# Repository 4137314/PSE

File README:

PSE - Power Supply Emulator
===========================

Version: 1.0
Author: 4137314
License: GNU General Public License v3.0

Purpose
-------
PSE is a KiCad project designed to emulate power supply circuits
for testing and prototyping purposes. It includes both schematic
and PCB layout files suitable for educational and development use.

Installation
------------
To obtain the project, clone the repository using Git:

    git clone https://github.com/4137314/PSE.git
    cd PSE

Open the file "PSE.kicad_pro" in KiCad to access the full project.

Usage
-----
- Inspect the schematic via "PSE.kicad_sch".
- Review the PCB layout in "PSE.kicad_pcb".
- Generate manufacturing files (Gerber, BOM, Drill) if needed.

Ensure all libraries and footprints referenced by the project are
available in your KiCad environment.

License
-------
This project is licensed under the GNU General Public License v3.0.
Refer to the LICENSE file in this repository for the full license text.

Reporting Bugs / Contributing
-----------------------------
Report bugs or suggest improvements via GitHub Issues. Contributions
are welcome under the same GPLv3 license.

Contact
-------
4137314
https://github.com/4137314/PSE

=======================================================================

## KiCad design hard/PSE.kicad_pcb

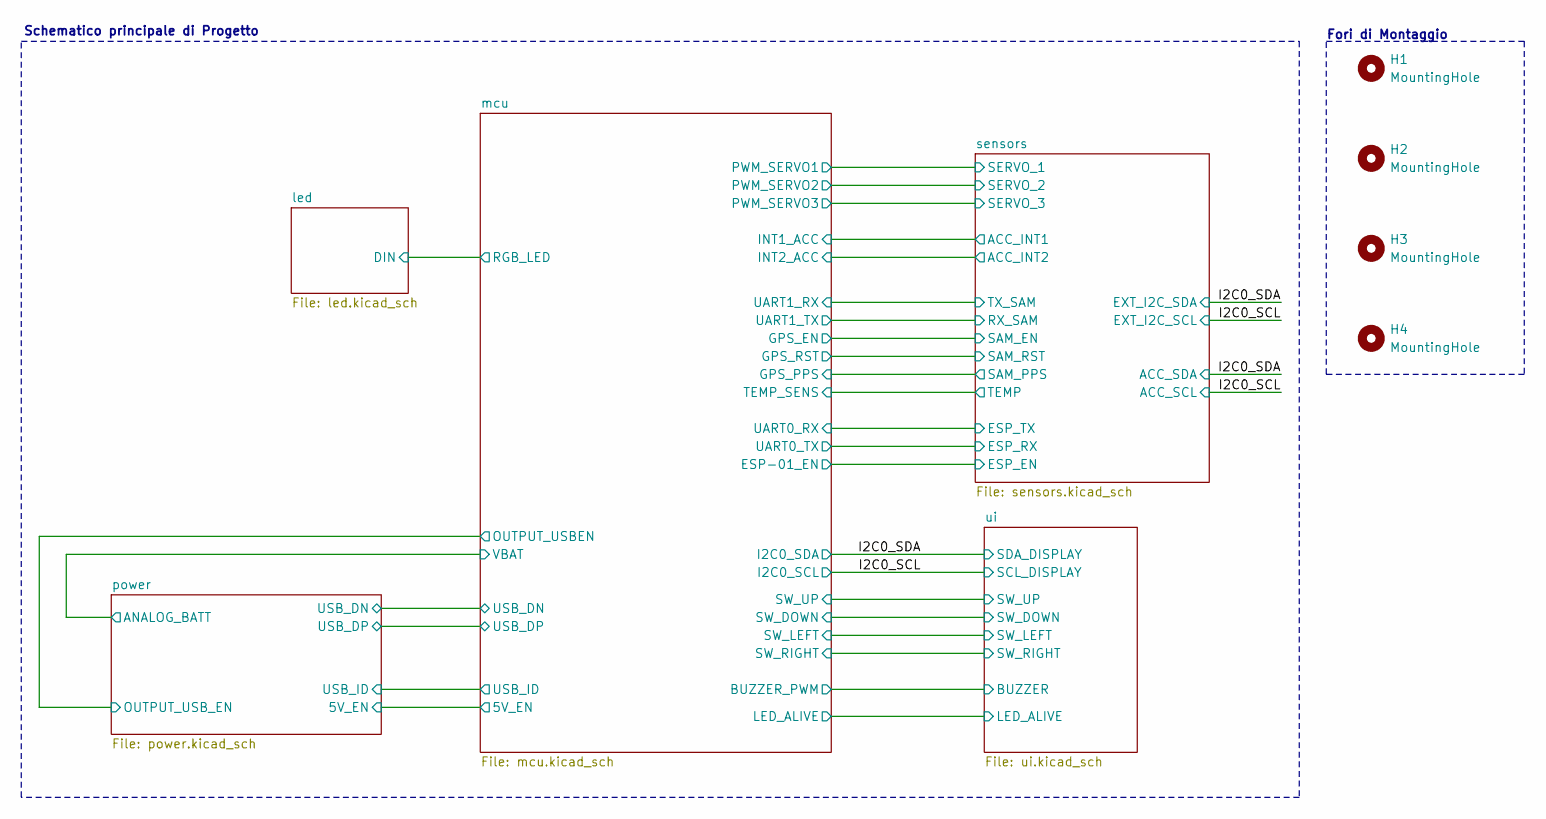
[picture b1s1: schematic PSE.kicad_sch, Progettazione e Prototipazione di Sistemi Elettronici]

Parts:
H1, H2, H3, H4: MountingHole; MountingHole_3.2mm_M3_Pad_Via

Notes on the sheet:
Fori di Montaggio
Schematico principale di Progetto

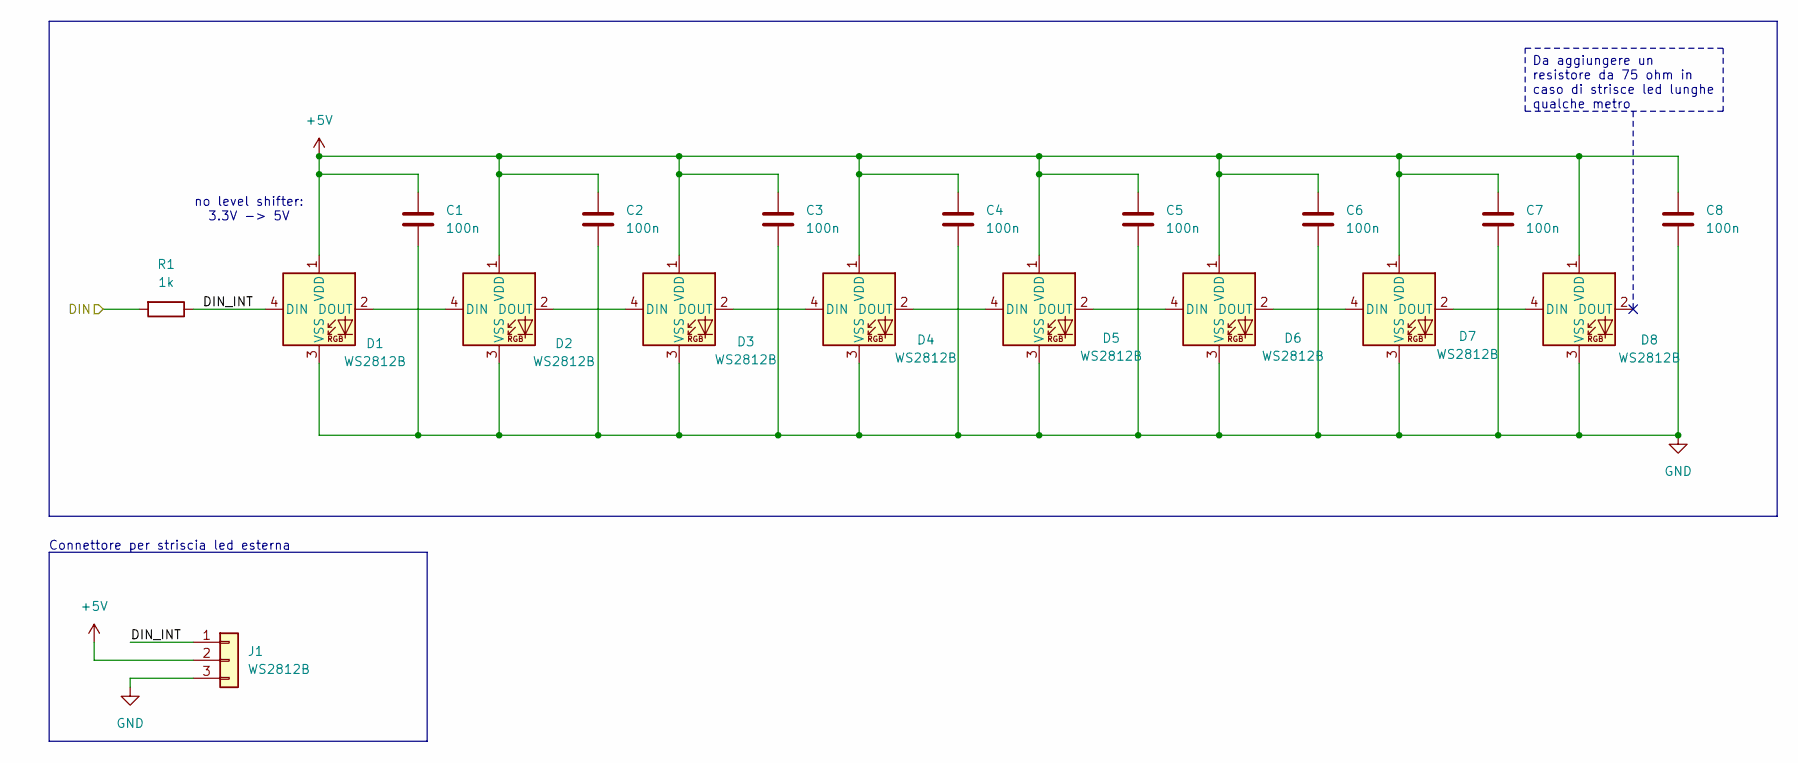
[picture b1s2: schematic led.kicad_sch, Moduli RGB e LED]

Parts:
C1, C2, C3, C4, C5, C6, C7, C8: 100n; C_0603_1608Metric
D1, D2, D3, D4, D5, D6, D7, D8: WS2812B; LED_WS2812B_PLCC4_5.0x5.0mm_P3.2mm
J1: WS2812B; PinHeader_1x03_P2.54mm_Vertical
R1: 1k; R_0603_1608Metric

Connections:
+5V: C1.1, C2.1, C3.1, C4.1, C5.1, C6.1, C7.1, C8.1, D1.1 (VDD), D2.1 (VDD), D3.1 (VDD), D4.1 (VDD), D5.1 (VDD), D6.1 (VDD), D7.1 (VDD), D8.1 (VDD), J1.2; also elsewhere on the board
/led/DIN: R1.2; also elsewhere on the board
/led/DIN_INT: D1.4 (DIN), J1.1, R1.1
GND: C1.2, C2.2, C3.2, C4.2, C5.2, C6.2, C7.2, C8.2, D1.3 (VSS), D2.3 (VSS), D3.3 (VSS), D4.3 (VSS), D5.3 (VSS), D6.3 (VSS), D7.3 (VSS), D8.3 (VSS), J1.3; also elsewhere on the board
unnamed: D1.2 (DOUT), D2.4 (DIN)
unnamed: D2.2 (DOUT), D3.4 (DIN)
unnamed: D3.2 (DOUT), D4.4 (DIN)
unnamed: D4.2 (DOUT), D5.4 (DIN)
unnamed: D5.2 (DOUT), D6.4 (DIN)
unnamed: D6.2 (DOUT), D7.4 (DIN)
unnamed: D7.2 (DOUT), D8.4 (DIN)

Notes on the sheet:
no level shifter: 3.3V -> 5V
Connettore per striscia led esterna
Da aggiungere un resistore da 75 ohm in caso di strisce led lunghe qualche metro

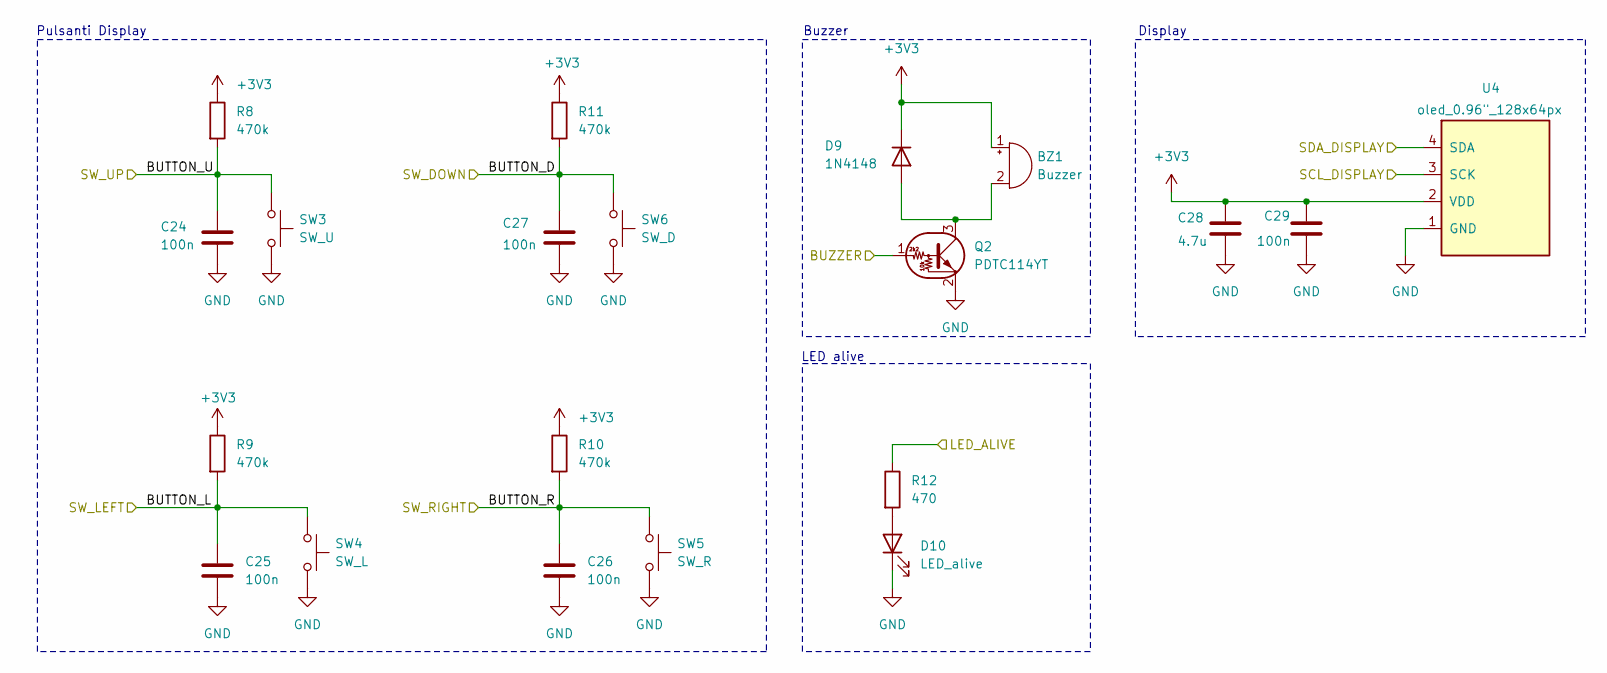
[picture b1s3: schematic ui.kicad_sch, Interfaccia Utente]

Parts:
BZ1: Buzzer; Buzzer_12x9.5RM7.6
C24, C25, C26, C27, C29: 100n; C_0603_1608Metric
C28: 4.7u; C_0603_1608Metric
D9: 1N4148; D_SOD-123
D10: LED_alive; LED_0603_1608Metric
Q2: PDTC114YT; SOT-23
R8, R9, R10, R11: 470k; R_0603_1608Metric
R12: 470; R_0603_1608Metric
SW3: SW_U; SW_SPST_EVQP0
SW4: SW_L; SW_SPST_EVQP0
SW5: SW_R; SW_SPST_EVQP0
SW6: SW_D; SW_SPST_EVQP0
U4: oled_0.96"_128x64px; PinHeader_1x04_P2.54mm_Vertical

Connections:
+3V3: BZ1.1 (+), C28.1, C29.1, D9.1 (K), R8.1, R9.1, R10.1, R11.1, U4.2 (VDD); also elsewhere on the board
/I2C0_SCL: U4.3 (SCK); also elsewhere on the board
/I2C0_SDA: U4.4 (SDA); also elsewhere on the board
/mcu/BUZZER_PWM: Q2.1 (B); also elsewhere on the board
/mcu/LED_ALIVE: R12.1; also elsewhere on the board
/ui/BUTTON_D: C27.1, R11.2, SW6.1; also elsewhere on the board
/ui/BUTTON_L: C25.1, R9.2, SW4.1; also elsewhere on the board
/ui/BUTTON_R: C26.1, R10.2, SW5.1; also elsewhere on the board
/ui/BUTTON_U: C24.1, R8.2, SW3.1; also elsewhere on the board
GND: C24.2, C25.2, C26.2, C27.2, C28.2, C29.2, D10.1 (K), Q2.2 (E), SW3.2, SW4.2, SW5.2, SW6.2, U4.1 (GND); also elsewhere on the board
unnamed: BZ1.2 (-), D9.2 (A), Q2.3 (C)
unnamed: D10.2 (A), R12.2

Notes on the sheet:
Pulsanti Display
Buzzer
Display
LED alive

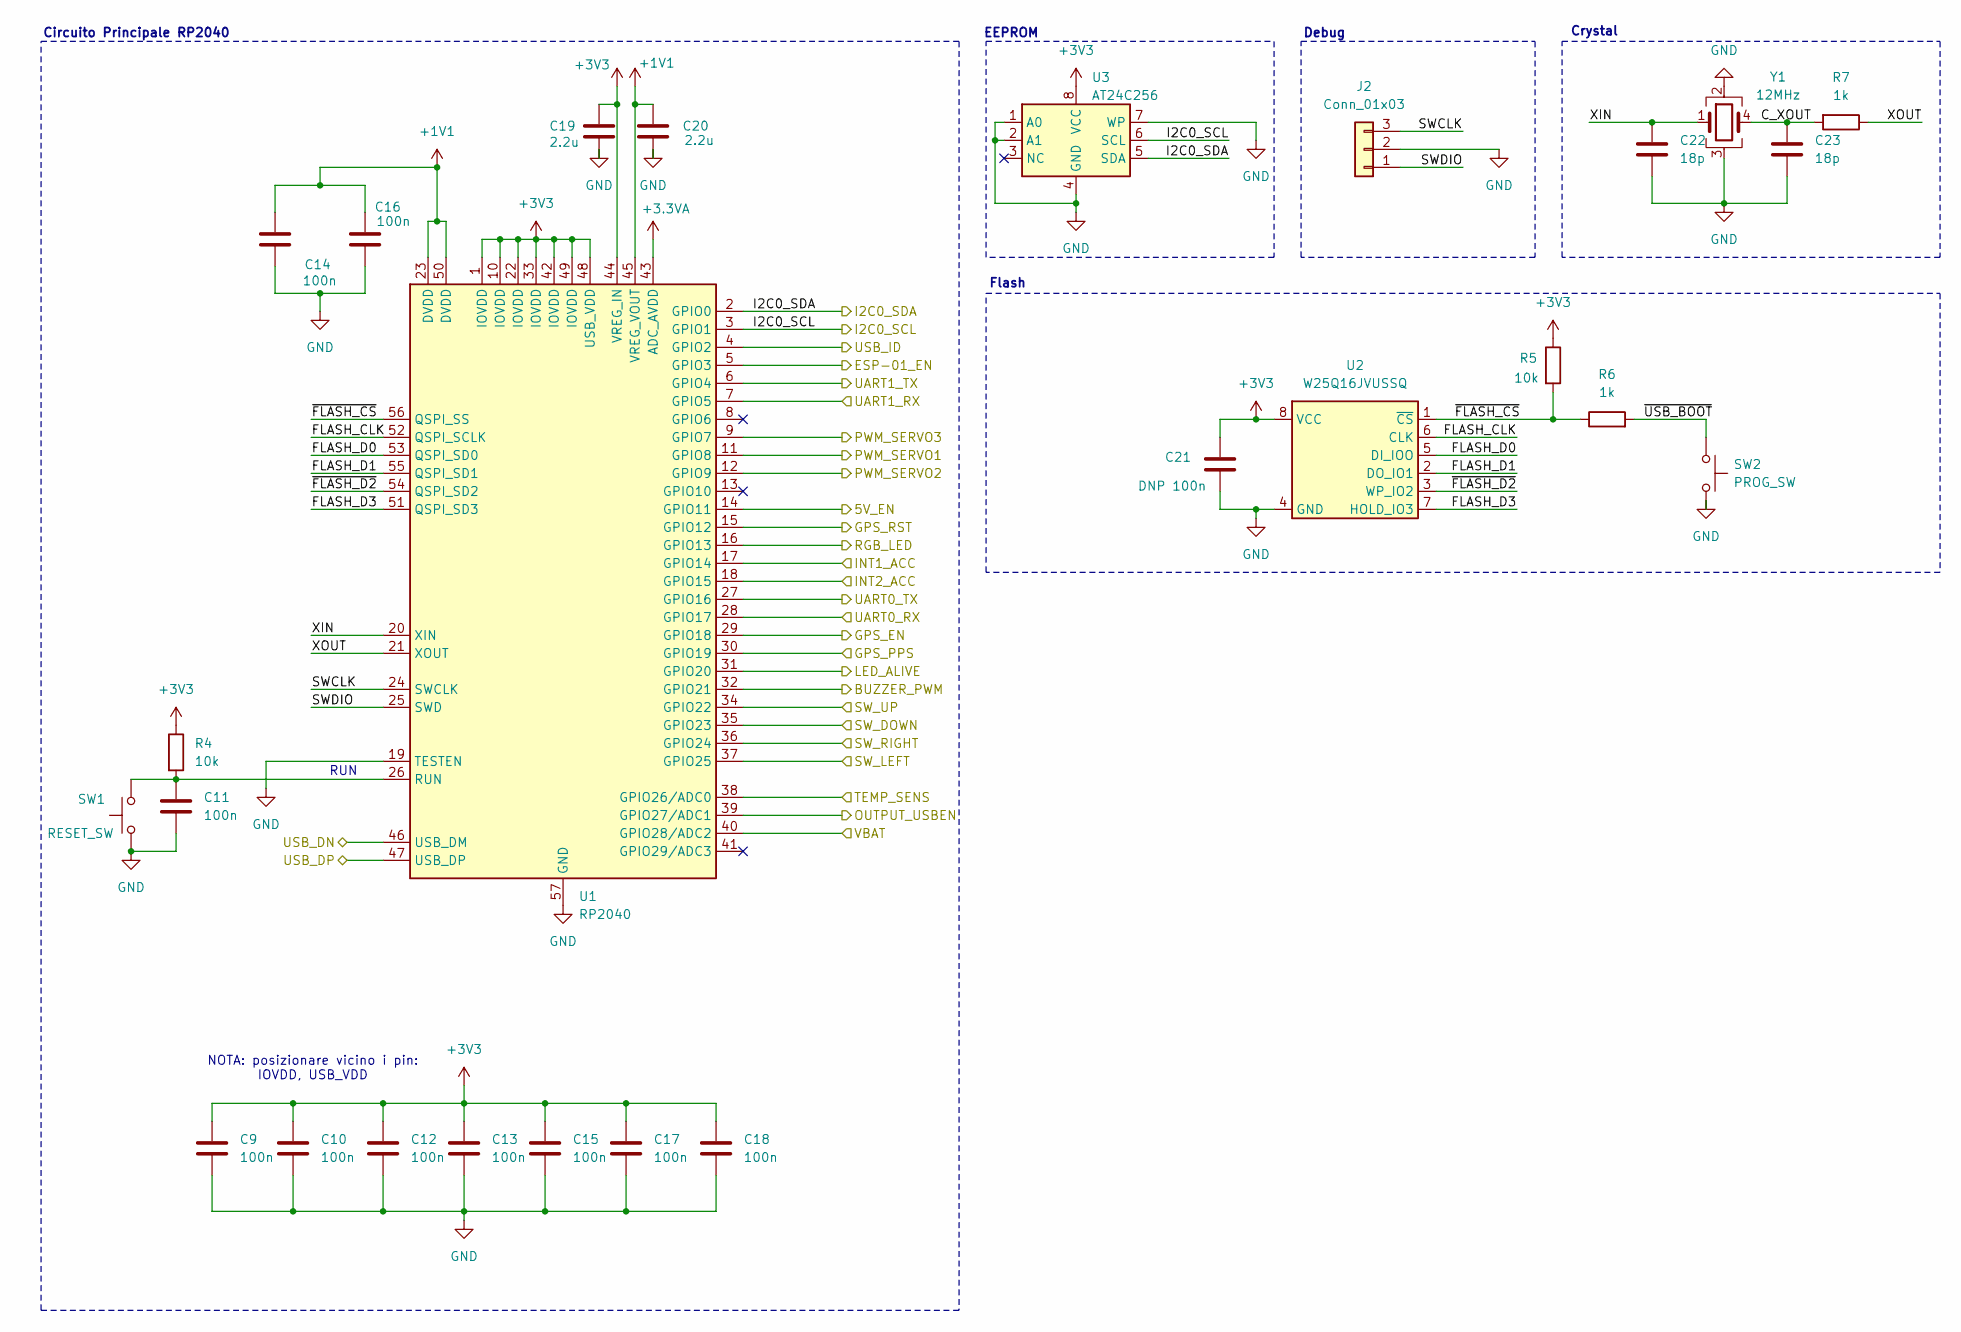
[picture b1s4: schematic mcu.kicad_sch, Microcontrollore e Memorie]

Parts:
C9, C10, C11, C12, C13, C14, C15, C16, C17, C18: 100n; C_0603_1608Metric
C19, C20: 2.2u; C_0603_1608Metric
C21: DNP 100n; C_0603_1608Metric
C22, C23: 18p; C_0603_1608Metric
J2: Conn_01x03; PinHeader_1x03_P2.54mm_Vertical
R4, R5: 10k; R_0603_1608Metric
R6, R7: 1k; R_0603_1608Metric
SW1: RESET_SW; SW_SPST_EVQP0
SW2: PROG_SW; SW_SPST_EVQP0
U1: RP2040; QFN-56-1EP_7x7mm_P0.4mm_EP3.2x3.2mm
U2: W25Q16JVUSSQ; SOIC-8_5.3x5.3mm_P1.27mm
U3: AT24C256; SOIC-8_3.9x4.9mm_P1.27mm
Y1: 12MHz; Crystal_SMD_3225-4Pin_3.2x2.5mm_HandSoldering

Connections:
+1V1: C14.1, C16.1, C20.1, U1.23 (DVDD), U1.45 (VREG_VOUT), U1.50 (DVDD)
+3.3VA: U1.43 (ADC_AVDD); also elsewhere on the board
+3V3: C9.1, C10.1, C12.1, C13.1, C15.1, C17.1, C18.1, C19.1, C21.1, R4.1, R5.1, U1.1 (IOVDD), U1.10 (IOVDD), U1.22 (IOVDD), U1.33 (IOVDD), U1.42 (IOVDD), U1.44 (VREG_IN), U1.48 (USB_VDD), U1.49 (IOVDD), U2.8 (VCC), U3.8 (VCC); also elsewhere on the board
/I2C0_SCL: U1.3 (GPIO1), U3.6 (SCL); also elsewhere on the board
/I2C0_SDA: U1.2 (GPIO0), U3.5 (SDA); also elsewhere on the board
/led/DIN: U1.16 (GPIO13); also elsewhere on the board
/mcu/5V_EN: U1.14 (GPIO11); also elsewhere on the board
/mcu/BUZZER_PWM: U1.32 (GPIO21); also elsewhere on the board
/mcu/C_XOUT: C23.1, R7.2, Y1.4
/mcu/ESP-01_EN: U1.5 (GPIO3); also elsewhere on the board
/mcu/FLASH_CLK: U1.52 (QSPI_SCLK), U2.6 (CLK)
/mcu/FLASH_D0: U1.53 (QSPI_SD0), U2.5 (DI_IOO)
/mcu/FLASH_D1: U1.55 (QSPI_SD1), U2.2 (DO_IO1)
/mcu/FLASH_D3: U1.51 (QSPI_SD3), U2.7 (HOLD_IO3)
/mcu/GPS_EN: U1.29 (GPIO18); also elsewhere on the board
/mcu/GPS_PPS: U1.30 (GPIO19); also elsewhere on the board
/mcu/GPS_RST: U1.15 (GPIO12); also elsewhere on the board
/mcu/INT1_ACC: U1.17 (GPIO14); also elsewhere on the board
/mcu/INT2_ACC: U1.18 (GPIO15); also elsewhere on the board
/mcu/LED_ALIVE: U1.31 (GPIO20); also elsewhere on the board
/mcu/OUTPUT_USBEN: U1.39 (GPIO27/ADC1); also elsewhere on the board
/mcu/PWM_SERVO1: U1.11 (GPIO8); also elsewhere on the board
/mcu/PWM_SERVO2: U1.12 (GPIO9); also elsewhere on the board
/mcu/PWM_SERVO3: U1.9 (GPIO7); also elsewhere on the board
/mcu/SWCLK: J2.3, U1.24 (SWCLK)
/mcu/SWDIO: J2.1, U1.25 (SWD)
/mcu/TEMP_SENS: U1.38 (GPIO26/ADC0); also elsewhere on the board
/mcu/UART0_RX: U1.28 (GPIO17); also elsewhere on the board
/mcu/UART0_TX: U1.27 (GPIO16); also elsewhere on the board
/mcu/USB_DN: U1.46 (USB_DM); also elsewhere on the board
/mcu/USB_DP: U1.47 (USB_DP); also elsewhere on the board
/mcu/USB_ID: U1.4 (GPIO2); also elsewhere on the board
/mcu/VBAT: U1.40 (GPIO28/ADC2); also elsewhere on the board
/mcu/XIN: C22.1, U1.20 (XIN), Y1.1
/mcu/XOUT: R7.1, U1.21 (XOUT)
/mcu/~FLASH_CS: R5.2, R6.1, U1.56 (QSPI_SS), U2.1 (~CS)
/mcu/~FLASH_D2: U1.54 (QSPI_SD2), U2.3 (WP_IO2)
/mcu/~USB_BOOT: R6.2, SW2.1
/sensors/UART_RX: U1.7 (GPIO5); also elsewhere on the board
/sensors/UART_TX: U1.6 (GPIO4); also elsewhere on the board
/ui/BUTTON_D: U1.35 (GPIO23); also elsewhere on the board
/ui/BUTTON_L: U1.37 (GPIO25); also elsewhere on the board
/ui/BUTTON_R: U1.36 (GPIO24); also elsewhere on the board
/ui/BUTTON_U: U1.34 (GPIO22); also elsewhere on the board
GND: C9.2, C10.2, C11.2, C12.2, C13.2, C14.2, C15.2, C16.2, C17.2, C18.2, C19.2, C20.2, C21.2, C22.2, C23.2, J2.2, SW1.1, SW2.2, U1.19 (TESTEN), U1.57 (GND), U2.4 (GND), U3.1 (A0), U3.2 (A1), U3.4 (GND), U3.7 (WP), Y1.2, Y1.3; also elsewhere on the board
unnamed: C11.1, R4.2, SW1.2, U1.26 (RUN)

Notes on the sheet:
Circuito Principale RP2040
Flash
Debug
NOTA: posizionare vicino i pin: IOVDD, USB_VDD
Crystal
RUN
EEPROM

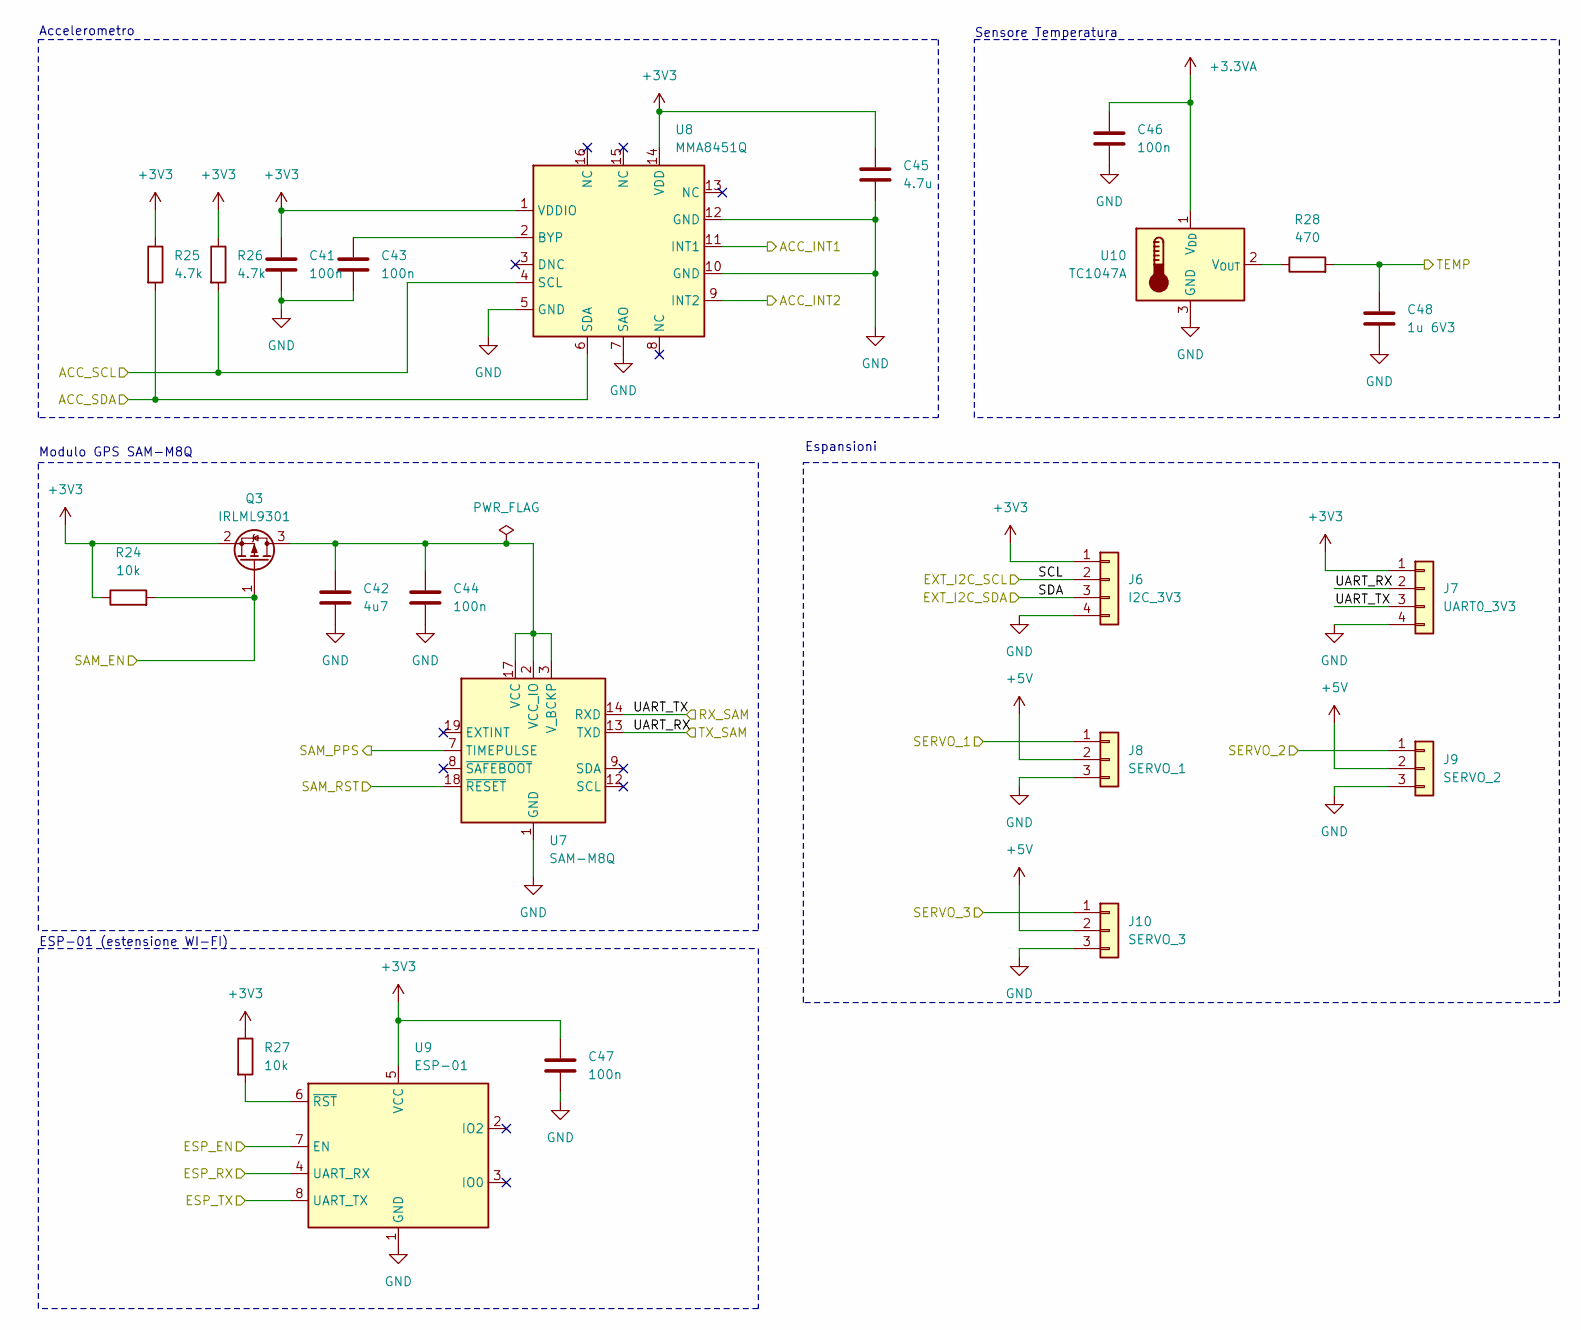
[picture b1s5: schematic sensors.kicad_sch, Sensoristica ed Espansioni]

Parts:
C41, C43, C44, C46, C47: 100n; C_0603_1608Metric
C42: 4u7; C_0603_1608Metric
C45: 4.7u; C_0603_1608Metric
C48: 1u 6V3; C_0603_1608Metric
J6: I2C_3V3; JST_XH_B4B-XH-A_1x04_P2.50mm_Vertical
J7: UART0_3V3; JST_XH_B4B-XH-A_1x04_P2.50mm_Vertical
J8: SERVO_1; PinHeader_1x03_P2.54mm_Vertical
J9: SERVO_2; PinHeader_1x03_P2.54mm_Vertical
J10: SERVO_3; PinHeader_1x03_P2.54mm_Vertical
Q3: IRLML9301; SOT-23
R24, R27: 10k; R_0603_1608Metric
R25, R26: 4.7k; R_0603_1608Metric
R28: 470; R_0603_1608Metric
U7: SAM-M8Q; ublox_SAM-M8Q
U8: MMA8451Q; QFN16_FRE
U9: ESP-01; PinSocket_2x04_P2.54mm_Vertical
U10: TC1047A; SOT-23

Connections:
+3.3VA: C46.1, U10.1 (V_{DD}); also elsewhere on the board
+3V3: C41.1, C45.1, C47.1, J6.1, J7.1, Q3.2 (S), R24.1, R25.1, R26.1, R27.1, U8.1 (VDDIO), U8.14 (VDD), U9.5 (VCC); also elsewhere on the board
+5V: J8.2, J9.2, J10.2; also elsewhere on the board
/I2C0_SCL: J6.2, R26.2, U8.4 (SCL); also elsewhere on the board
/I2C0_SDA: J6.3, R25.2, U8.6 (SDA); also elsewhere on the board
/mcu/ESP-01_EN: U9.7 (EN); also elsewhere on the board
/mcu/GPS_EN: Q3.1 (G), R24.2; also elsewhere on the board
/mcu/GPS_PPS: U7.7 (TIMEPULSE); also elsewhere on the board
/mcu/GPS_RST: U7.18 (~RESET); also elsewhere on the board
/mcu/INT1_ACC: U8.11 (INT1); also elsewhere on the board
/mcu/INT2_ACC: U8.9 (INT2); also elsewhere on the board
/mcu/PWM_SERVO1: J8.1; also elsewhere on the board
/mcu/PWM_SERVO2: J9.1; also elsewhere on the board
/mcu/PWM_SERVO3: J10.1; also elsewhere on the board
/mcu/TEMP_SENS: C48.1, R28.2; also elsewhere on the board
/mcu/UART0_RX: U9.8 (UART_TX); also elsewhere on the board
/mcu/UART0_TX: U9.4 (UART_RX); also elsewhere on the board
/sensors/UART_RX: J7.2, U7.13 (TXD); also elsewhere on the board
/sensors/UART_TX: J7.3, U7.14 (RXD); also elsewhere on the board
GND: C41.2, C42.2, C43.2, C44.2, C45.2, C46.2, C47.2, C48.2, J6.4, J7.4, J8.3, J9.3, J10.3, U7.1 (GND), U8.5 (GND), U8.7 (SAO), U8.10 (GND), U8.12 (GND), U9.1 (GND), U10.3 (GND); also elsewhere on the board
unnamed: C42.1, C44.1, Q3.3 (D), U7.2 (VCC_IO), U7.3 (V_BCKP), U7.17 (VCC)
unnamed: C43.1, U8.2 (BYP)
unnamed: R27.2, U9.6 (~RST)
unnamed: R28.1, U10.2 (V_{OUT})

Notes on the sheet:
Sensore Temperatura
Accelerometro
ESP-01 (estensione WI-FI)
Modulo GPS SAM-M8Q
Espansioni

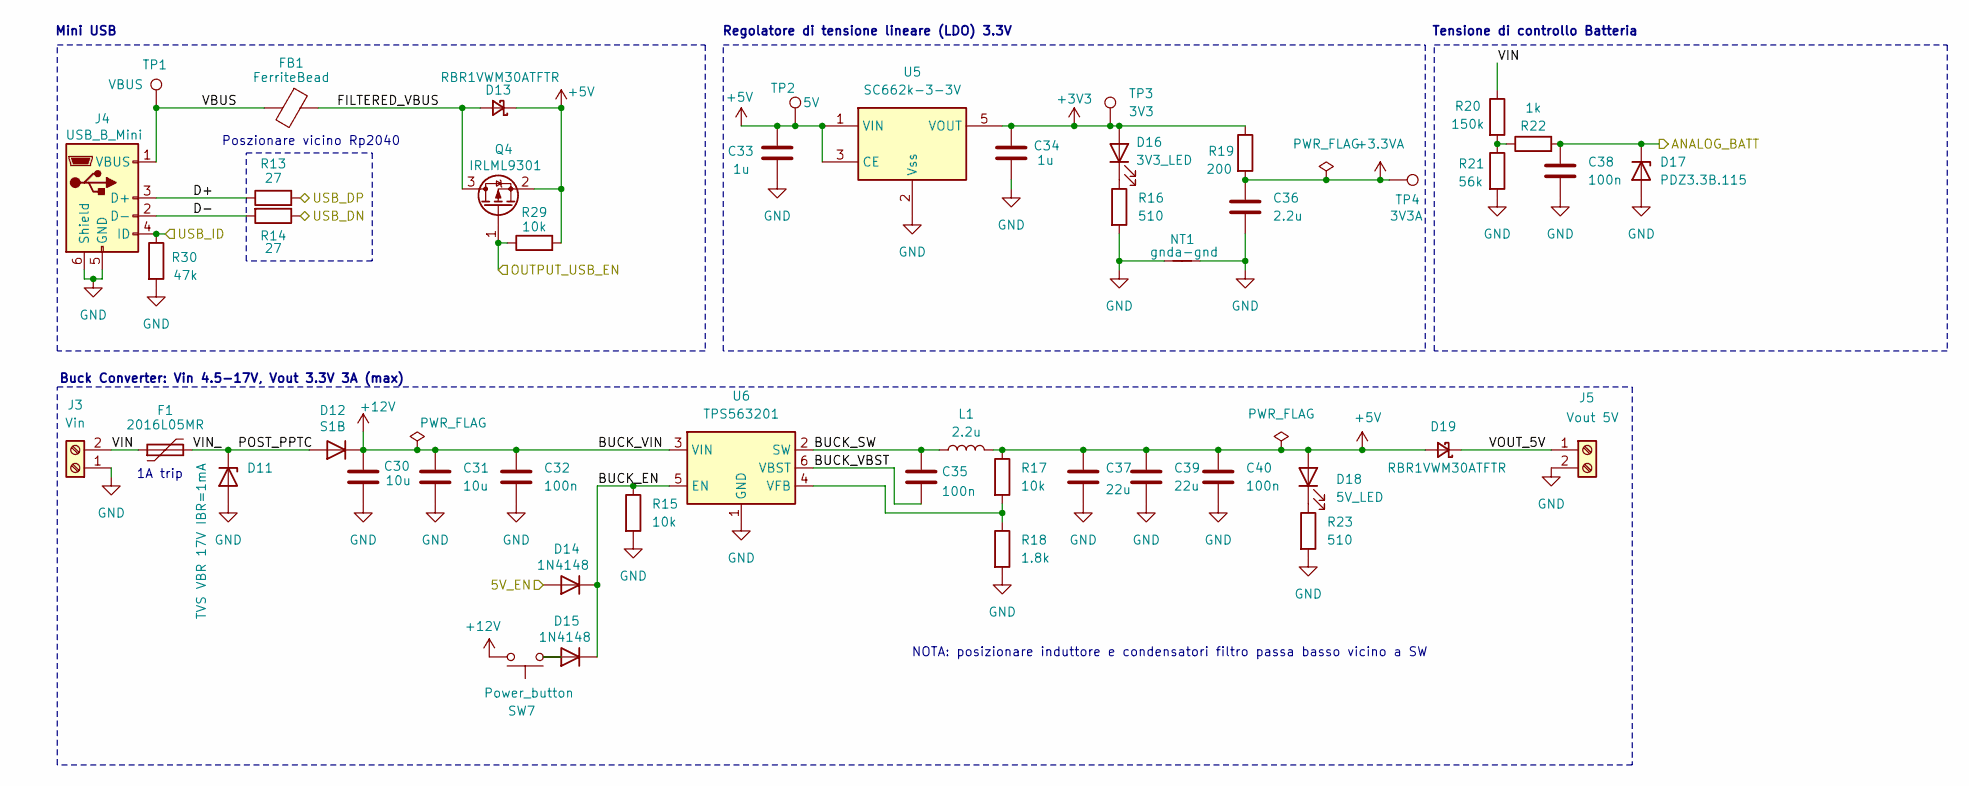
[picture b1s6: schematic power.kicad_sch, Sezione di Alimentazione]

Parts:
C30, C31: 10u; C_0805_2012Metric
C32, C35, C38, C40: 100n; C_0603_1608Metric
C33, C34: 1u; C_0603_1608Metric
C36: 2.2u; C_0603_1608Metric
C37, C39: 22u; C_0805_2012Metric
D11: TVS VBR 17V IBR=1mA; D_SMA
D12: S1B; D_SMA
D13, D19: RBR1VWM30ATFTR; D_SOD-123
D14, D15: 1N4148; D_SOD-123
D16: 3V3_LED; LED_0805_2012Metric
D17: PDZ3.3B.115; D_SOD-323_HandSoldering
D18: 5V_LED; LED_0805_2012Metric
F1: 2016L05MR; Fuse_1206_3216Metric
FB1: FerriteBead; C_0805_2012Metric
J3: Vin; TerminalBlock_bornier-2_P5.08mm
J4: USB_B_Mini; USB_Mini-B_Wuerth_65100516121_Horizontal
J5: Vout 5V; TerminalBlock_bornier-2_P5.08mm
L1: 2.2u; C_0603_1608Metric
NT1: gnda-gnd; NetTie-2_SMD_Pad0.5mm
Q4: IRLML9301; SOT-23
R13, R14: 27; R_0603_1608Metric
R15, R17, R29: 10k; R_0603_1608Metric
R16, R23: 510; R_0603_1608Metric
R18: 1.8k; R_0603_1608Metric
R19: 200; R_0603_1608Metric
R20: 150k; R_0603_1608Metric
R21: 56k; R_0603_1608Metric
R22: 1k; R_0603_1608Metric
R30: 47k; R_0603_1608Metric
SW7: Power_button; SW_SPST_EVQP0
TP1: VBUS; TestPoint_THTPad_D1.5mm_Drill0.7mm
TP2: 5V; TestPoint_THTPad_D1.5mm_Drill0.7mm
TP3: 3V3; TestPoint_THTPad_D1.5mm_Drill0.7mm
TP4: 3V3A; TestPoint_THTPad_D1.5mm_Drill0.7mm
U5: SC662k-3-3V; SOT-23-5_HandSoldering
U6: TPS563201; SOT-23-6

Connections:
+3.3VA: C36.1, R19.2, TP4.1; also elsewhere on the board
+3V3: C34.1, D16.2 (A), R19.1, TP3.1, U5.5 (VOUT); also elsewhere on the board
+5V: C33.1, C37.1, C39.1, C40.1, D13.1 (K), D18.2 (A), D19.2 (A), L1.2, Q4.2 (S), R17.1, R29.2, TP2.1, U5.1 (VIN), U5.3 (CE); also elsewhere on the board
+12V: C30.1, C31.1, C32.1, D12.1 (K), SW7.2, U6.3 (VIN)
/mcu/5V_EN: D14.2 (A); also elsewhere on the board
/mcu/OUTPUT_USBEN: Q4.1 (G), R29.1; also elsewhere on the board
/mcu/USB_DN: R14.1; also elsewhere on the board
/mcu/USB_DP: R13.2; also elsewhere on the board
/mcu/USB_ID: J4.4 (ID), R30.1; also elsewhere on the board
/mcu/VBAT: C38.1, D17.1 (K), R22.2; also elsewhere on the board
/power/BUCK_EN: D14.1 (K), D15.1 (K), R15.1, U6.5 (EN)
/power/BUCK_SW: C35.2, L1.1, U6.2 (SW)
/power/BUCK_VBST: C35.1, U6.6 (VBST)
/power/D+: J4.3 (D+), R13.1
/power/D-: J4.2 (D-), R14.2
/power/FILTERED_VBUS: D13.2 (A), FB1.1, Q4.3 (D)
/power/POST_PPTC: D11.1 (K), D12.2 (A), F1.2
/power/VBUS: FB1.2, J4.1 (VBUS), TP1.1
/power/VIN: F1.1, J3.2, R20.1
/power/VOUT_5V: D19.1 (K), J5.1
GND: C30.2, C31.2, C32.2, C33.2, C34.2, C36.2, C37.2, C38.2, C39.2, C40.2, D11.2 (A), D17.2 (A), J3.1, J4.5 (GND), J4.6 (Shield), J5.2, NT1.1, NT1.2, R15.2, R16.2, R18.2, R21.2, R23.2, R30.2, U5.2 (Vss), U6.1 (GND); also elsewhere on the board
unnamed: D15.2 (A), SW7.1
unnamed: D16.1 (K), R16.1
unnamed: D18.1 (K), R23.1
unnamed: R20.2, R21.1, R22.1
unnamed: R17.2, R18.1, U6.4 (VFB)

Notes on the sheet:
Tensione di controllo Batteria
Regolatore di tensione lineare (LDO) 3.3V
Buck Converter: Vin 4.5-17V, Vout 3.3V 3A (max)
Poszionare vicino Rp2040
NOTA: posizionare induttore e condensatori filtro passa basso vicino a SW
1A trip
Mini USB

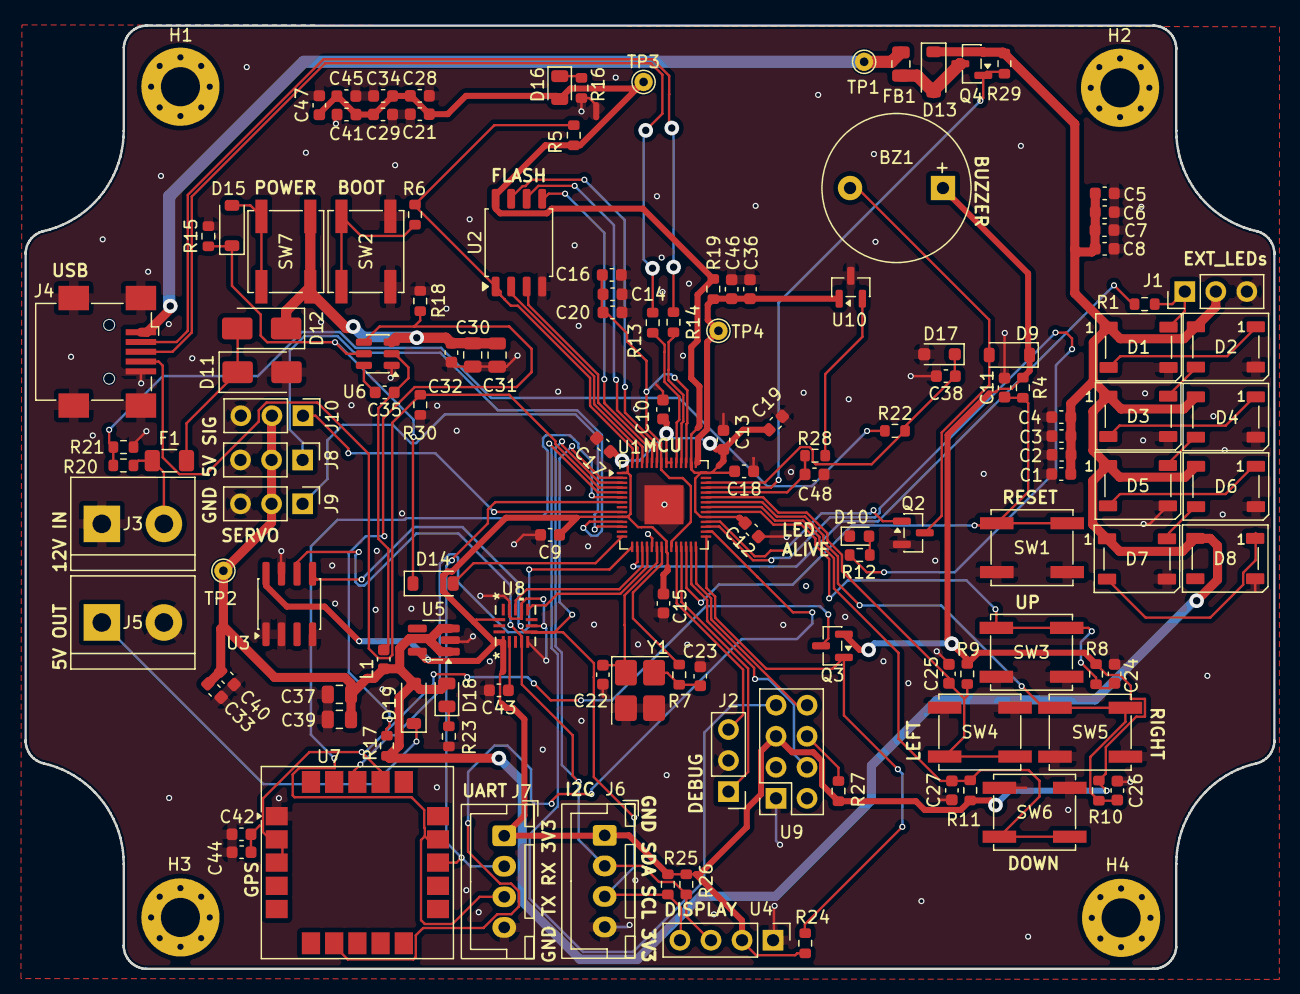
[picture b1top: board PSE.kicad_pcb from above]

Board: 2 copper layers, 102.2 x 77.2 mm, 139 parts (0 on the bottom side), 77 nets.

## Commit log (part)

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2025-09-27 edit
2026-06-18 update - se ci sono errori prima della consegna -> (flag prima di sto commit funzionava tutto)
